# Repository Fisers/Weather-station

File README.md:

# Weather Station
## Included sensors
- Wind Direction (NRG #200P)
- Anenometer (NRG #40)
- Humidity (HIH8131)
- Temperature (HIH8131)
- Atmospheric pressure (BMP280)
## Interface methods
- Ethernet TCP
  - Website interface
  - TCP packets to the server
- Nokia 5110 display
- SD card data logging in CSV format
- ~~USB to UART (For debugging and programming with bootloader)~~ See issues #1
## Power supply
- 100V - 240V AC
- 3.3V DC
## Extras
- Real Time Clock
- Easy calibration using buttons
- Space Invaders minigame
- No easter eggs
## Free PINs for future upgrades
- PB0 (Timer 0) | PA3 (ADC) | PA4 (ADC) | PA5 (ADC) | PA6 (ADC) | PA7 (ADC)
- Motherboard also has free connections to 3.3v and GND aswell as SPI.

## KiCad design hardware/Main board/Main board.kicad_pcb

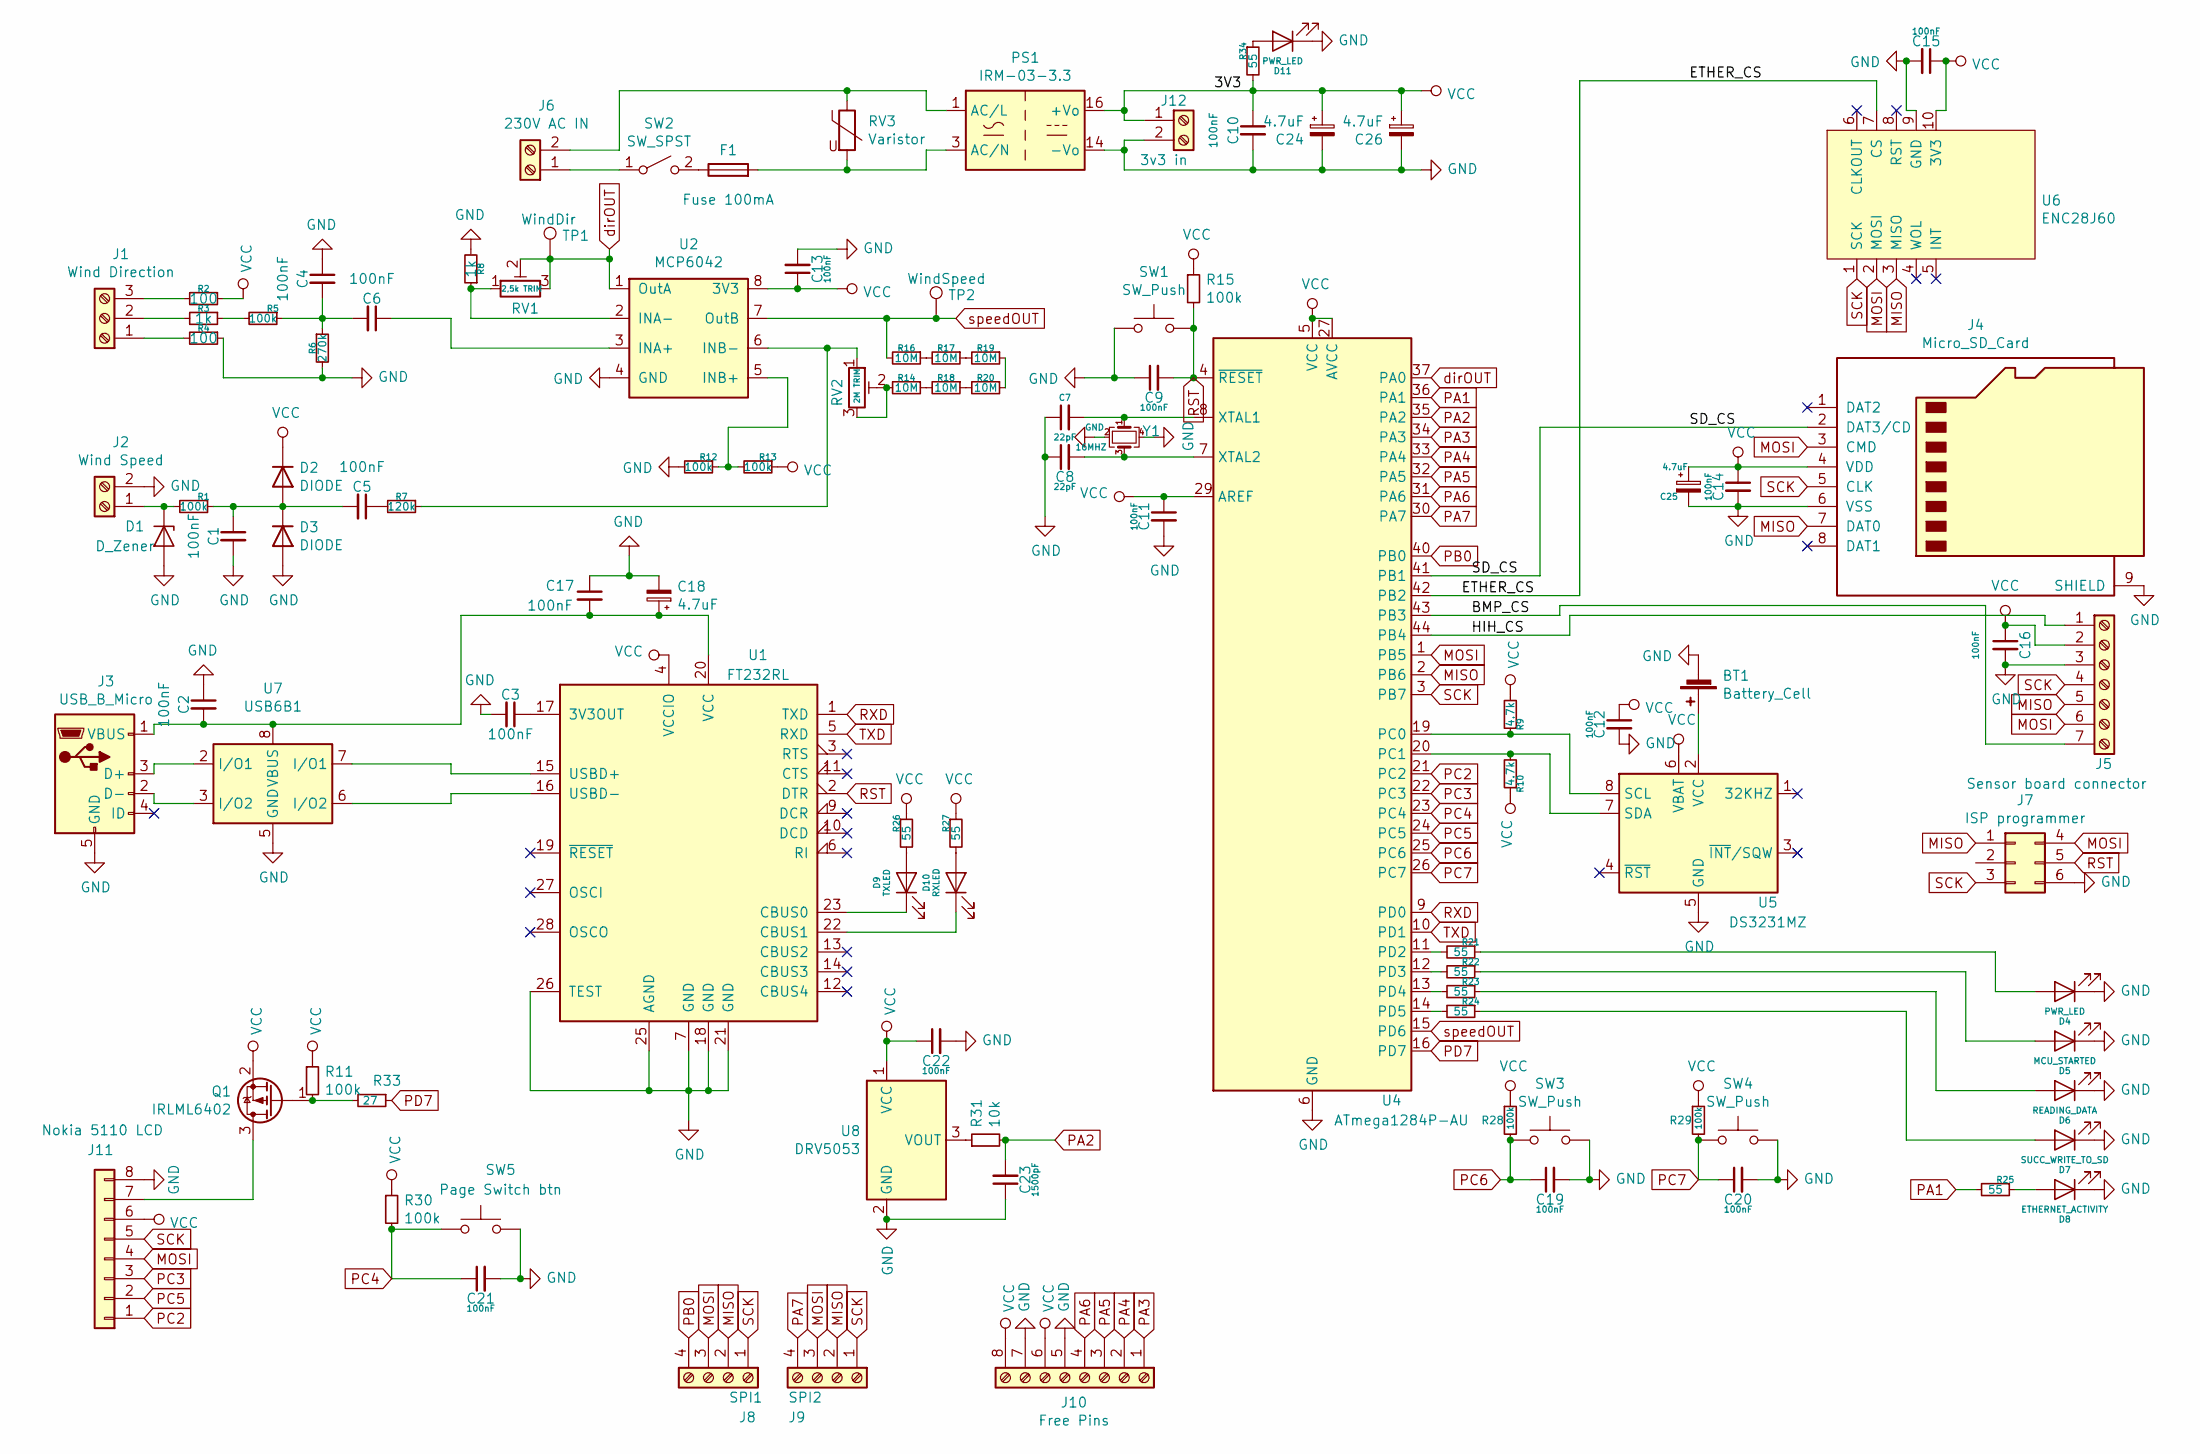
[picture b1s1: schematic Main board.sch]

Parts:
BT1: Battery_Cell; BatteryHolder_Keystone_106_1x20mm
C1, C2, C3, C4, C5, C6, C9, C10, C11, C12, C13, C14, C15, C16, C17, C19, C20, C21, C22: 100nF; C_0805_2012Metric_Pad1.15x1.40mm_HandSolder
C7, C8: 22pF; C_0805_2012Metric_Pad1.15x1.40mm_HandSolder
C18: 4.7uF; CP_Elec_4x5.3
C23: 1500pF; C_0805_2012Metric_Pad1.15x1.40mm_HandSolder
C24, C25, C26: 4.7uF; CP_Elec_4x5.4
D1: D_Zener; D_0805_2012Metric
D2, D3: DIODE; D_0805_2012Metric
D4, D11: PWR_LED; D_0805_2012Metric
D5: MCU_STARTED; D_0805_2012Metric
D6: READING_DATA; D_0805_2012Metric
D7: SUCC_WRITE_TO_SD; D_0805_2012Metric
D8: ETHERNET_ACTIVITY; D_0805_2012Metric
D9: TXLED; D_0805_2012Metric
D10: RXLED; D_0805_2012Metric
F1: Fuse 100mA; Fuseholder_Cylinder-5x20mm_Schurter_0031_8201_Horizontal_Op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
J1: Wind Direction; TerminalBlock_Altech_AK300-4_P5.00mm
J2: Wind Speed; TerminalBlock_Altech_AK300-2_P5.00mm
J3: USB_B_Micro; KYCON_KMMVX-SMT-BS-BTR
J4: Micro_SD_Card; microSD
J5: Sensor board connector; TerminalBlock_Phoenix_MKDS-1,5-8_1x08_P5.00mm_Horizontal
J6: 230V AC IN; TerminalBlock_RND_205-00298_1x02_P10.00mm_Horizontal
J7: ISP programmer; PinHeader_2x03_P2.54mm_Vertical
J8: SPI1; TerminalBlock_Altech_AK300-4_P5.00mm
J9: SPI2; TerminalBlock_Altech_AK300-4_P5.00mm
J10: Free Pins; TerminalBlock_Phoenix_MKDS-1,5-8_1x08_P5.00mm_Horizontal
J11: Nokia 5110 LCD; Nokia_5110_LCD
J12: 3v3 in; TerminalBlock_Altech_AK300-2_P5.00mm
PS1: IRM-03-3.3; Converter_ACDC_MeanWell_IRM-03-xx_THT
Q1: IRLML6402; SOT-23
R1, R5, R11, R12, R13, R15, R28, R29, R30: 100k; R_0805_2012Metric
R2, R4: 100; R_0805_2012Metric
R3, R8: 1k; R_0805_2012Metric
R6: 270k; R_0805_2012Metric
R7: 120k; R_0805_2012Metric
R9, R10: 4.7k; R_0805_2012Metric
R14, R16, R17, R18, R19, R20: 10M; R_0805_2012Metric
R21, R22, R23, R24, R25, R26, R27, R34: 55; R_0805_2012Metric
R31: 10k; R_0805_2012Metric
R33: 27; R_0805_2012Metric
RV1: 2,5k TRIM; Potentiometer_Bourns_3314G_Vertical
RV2: 2M TRIM; Potentiometer_Bourns_3224W_Vertical
RV3: Varistor; Varistor_SMD
SW1, SW3, SW4: SW_Push; SW_Push_1P1T_NO_6x6mm_H9.5mm
SW2: SW_SPST; Switch_NEW
SW5: Page Switch btn; SW_Push_1P1T_NO_6x6mm_H9.5mm
TP1: WindDir; Test_Pad
TP2: WindSpeed; Test_Pad
U1: FT232RL; SSOP-28_5.3x10.2mm_P0.65mm
U2: MCP6042; MCP6042-E&slash_P
U4: ATmega1284P-AU; TQFP-44_10x10mm_P0.8mm
U5: DS3231MZ; SOIC-8_3.9x4.9mm_P1.27mm
U6: ENC28J60
U7: USB6B1; SOIC-8_3.9x4.9mm_P1.27mm
U8: DRV5053; PinSocket_1x03_P2.54mm_Vertical
Y1: 16MHZ; Crystal_SMD

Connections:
/BMP_CS: J5.7, U4.43 (PB3)
/ETHER_CS: U4.42 (PB2), U6.7 (CS)
/HIH_CS: J5.1, U4.44 (PB4)
/SD_CS: J4.2 (DAT3/CD), U4.41 (PB1)
GND: BT1.2 (-), C1.2, C2.1, C3.2, C4.1, C7.1, C8.1, C9.1, C10.2, C11.2, C12.2, C13.2, C14.2, C15.2, C16.2, C17.1, C18.2, C19.2, C20.2, C21.2, C22.2, C23.1, C24.2, C25.2, C26.2, D1.2 (A), D3.1 (A), D4.1 (K), D5.1 (K), D6.1 (K), D7.1 (K), D8.1 (K), D11.1 (K), J2.2, J3.5 (GND), J4.6 (VSS), J4.9 (SHIELD), J5.3, J7.6, J10.5, J10.7, J11.8, J12.2, PS1.14 (-Vo), R4.1, R6.2, R8.2, R12.2, SW1.1, SW3.2, SW4.2, SW5.2, U1.7 (GND), U1.18 (GND), U1.21 (GND), U1.25 (AGND), U1.26 (TEST), U2.4 (GND), U4.6 (GND), U4.18 (GND), U4.28 (GND), U4.39 (GND), U5.5 (GND), U6.9 (GND), U7.4 (GND), U7.5 (GND), U8.2 (GND), Y1.2, Y1.4
MISO: J4.7 (DAT0), J5.5, J7.1, J8.2, J9.2, U4.2 (PB6), U6.3 (MISO)
MOSI: J4.3 (CMD), J5.6, J7.4, J8.3, J9.3, J11.4, U4.1 (PB5), U6.2 (MOSI)
unnamed: BT1.1 (+), U5.2 (VCC)
unnamed: C1.1, C5.2, D2.1 (A), D3.2 (K), R1.1
unnamed: C3.1, U1.17 (3V3OUT)
unnamed: C4.2, C6.2, R5.1, R6.1
unnamed: C5.1, R7.2
unnamed: C6.1, U2.3 (INA+)
unnamed: C7.2, U4.8 (XTAL1), Y1.1
unnamed: C8.2, U4.7 (XTAL2), Y1.3
unnamed: C2.2, C17.2, C18.1, J3.1 (VBUS), U1.20 (VCC), U7.1 (VBUS), U7.8 (VBUS)
unnamed: D1.1 (K), J2.1, R1.2
unnamed: D4.2 (A), R21.1
unnamed: D5.2 (A), R22.1
unnamed: D6.2 (A), R23.1
unnamed: D7.2 (A), R24.1
unnamed: D8.2 (A), R25.1
unnamed: D9.1 (K), U1.23 (CBUS0)
unnamed: D9.2 (A), R26.2
unnamed: D10.1 (K), U1.22 (CBUS1)
unnamed: D10.2 (A), R27.2
unnamed: D11.2 (A), R34.1
unnamed: F1.1, SW2.2 (B)
unnamed: F1.2, PS1.3 (AC/N), RV3.2
unnamed: J1.1, R4.2
unnamed: J1.2, R3.2
unnamed: J1.3, R2.2
unnamed: J3.2 (D-), U7.3 (I/O2)
unnamed: J3.3 (D+), U7.2 (I/O1)
unnamed: J6.1, SW2.1 (A)
unnamed: J6.2, PS1.1 (AC/L), RV3.1
unnamed: J11.7, Q1.3 (D)
unnamed: Q1.1 (G), R11.2, R33.2
unnamed: R3.1, R5.2
unnamed: R7.1, RV2.1, U2.6 (INB-)
unnamed: R8.1, RV1.1, U2.2 (INA-)
unnamed: R9.1, U4.19 (PC0), U5.8 (SCL)
unnamed: R10.2, U4.20 (PC1), U5.7 (SDA)
unnamed: R12.1, R13.2, U2.5 (INB+)
unnamed: R14.1, R18.2
unnamed: R14.2, RV2.2, RV2.3
unnamed: R16.1, R17.2
unnamed: R17.1, R19.2
unnamed: R18.1, R20.2
unnamed: R19.1, R20.1
unnamed: R21.2, U4.11 (PD2)
unnamed: R22.2, U4.12 (PD3)
unnamed: R23.2, U4.13 (PD4)
unnamed: R24.2, U4.14 (PD5)
unnamed: R31.1, U8.3 (VOUT)
unnamed: U1.15 (USBD+), U7.7 (I/O1)
unnamed: U1.16 (USBD-), U7.6 (I/O2)
PA1: R25.2, U4.36 (PA1)
PA2: C23.2, R31.2, U4.35 (PA2)
PA3: J10.1, U4.34 (PA3)
PA4: J10.2, U4.33 (PA4)
PA5: J10.3, U4.32 (PA5)
PA6: J10.4, U4.31 (PA6)
PA7: J9.4, U4.30 (PA7)
PB0: J8.4, U4.40 (PB0)
PC2: J11.1, U4.21 (PC2)
PC3: J11.3, U4.22 (PC3)
PC4: C21.1, R30.2, SW5.1, U4.23 (PC4)
PC5: J11.2, U4.24 (PC5)
PC6: C19.1, R28.2, SW3.1, U4.25 (PC6)
PC7: C20.1, R29.2, SW4.1, U4.26 (PC7)
PD7: R33.1, U4.16 (PD7)
RST: C9.2, J7.5, R15.2, SW1.2, U1.2 (DTR), U4.4 (~RESET)
RXD: U1.1 (TXD), U4.9 (PD0)
SCK: J4.5 (CLK), J5.4, J7.3, J8.1, J9.1, J11.5, U4.3 (PB7), U6.1 (SCK)
TXD: U1.5 (RXD), U4.10 (PD1)
VCC: C10.1, C11.1, C12.1, C13.1, C14.1, C15.1, C16.1, C22.1, C24.1, C25.1, C26.1, D2.2 (K), J4.4 (VDD), J5.2, J10.6, J10.8, J11.6, J12.1, PS1.16 (+Vo), Q1.2 (S), R2.1, R9.2, R10.1, R11.1, R13.1, R15.1, R26.1, R27.1, R28.1, R29.1, R30.1, R34.2, U1.4 (VCCIO), U2.8 (3V3), U4.5 (VCC), U4.17 (VCC), U4.27 (AVCC), U4.29 (AREF), U4.38 (VCC), U5.6 (VBAT), U6.10 (3V3), U8.1 (VCC)
dirOUT: RV1.2, RV1.3, TP1.1, U2.1 (OutA), U4.37 (PA0)
speedOUT: R16.2, TP2.1, U2.7 (OutB), U4.15 (PD6)

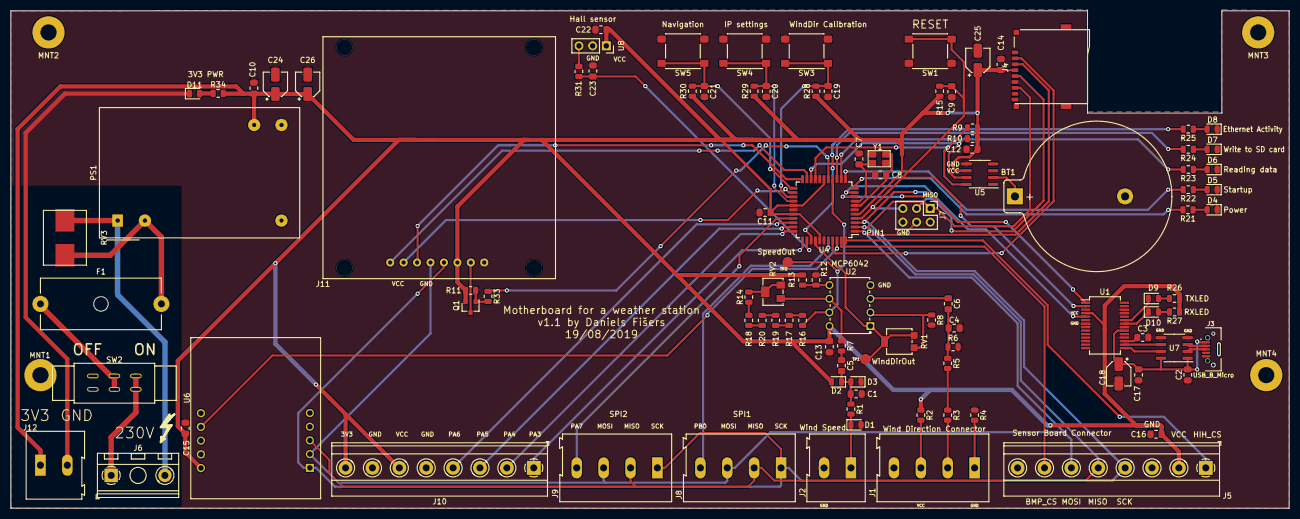
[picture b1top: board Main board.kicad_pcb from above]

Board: 2 copper layers, 237.8 x 92.5 mm, 108 parts (0 on the bottom side), 79 nets.

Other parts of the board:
MNT1, MNT2, MNT3, MNT4: MountingHole_3mm_Pad

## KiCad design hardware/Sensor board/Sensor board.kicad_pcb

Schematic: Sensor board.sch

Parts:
C1, C2: C_Small; C_0805_2012Metric_Pad1.15x1.40mm_HandSolder
J1: Conn_01x07_Female; PinSocket_1x07_P2.54mm_Vertical
J2: bmp280; PinSocket_1x07_P2.54mm_Vertical
R1: R_Small; R_0805_2012Metric_Pad1.15x1.40mm_HandSolder
U1: HIH8130; SOIC-8_3.9x4.9mm_P1.27mm

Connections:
/BMP280_CS: J1.7, J2.7
/CLK: J1.4, J2.4, U1.4
/MISO: J1.5, J2.5, U1.5
/MOSI: J1.6, J2.6
GND: C1.1, C2.1, J1.3, J2.3, U1.2
unnamed: C2.2, U1.1
unnamed: J1.1, R1.2, U1.3
VCC: C1.2, J1.2, J2.2, R1.1, U1.8

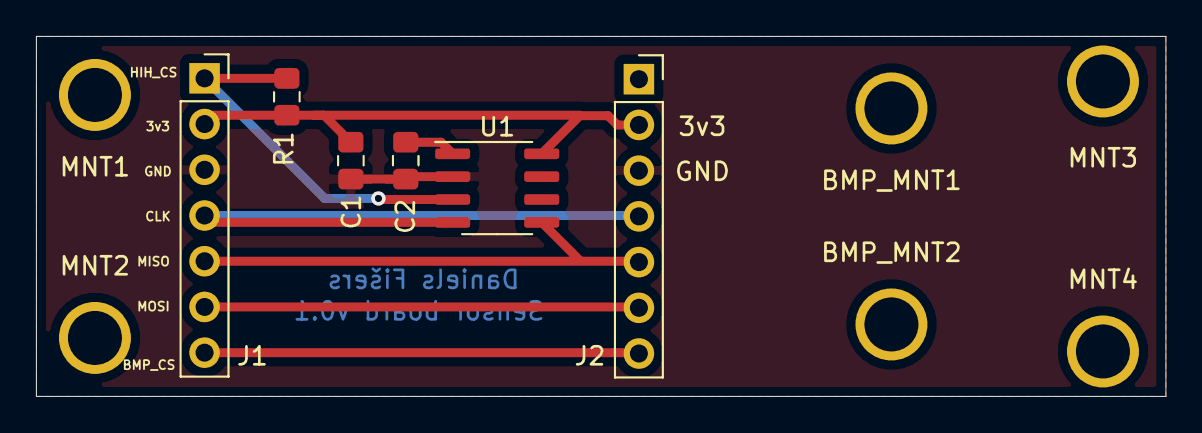
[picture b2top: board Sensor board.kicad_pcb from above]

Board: 2 copper layers, 62.8 x 20.0 mm, 12 parts (0 on the bottom side), 8 nets.

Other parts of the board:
BMP_MNT1, BMP_MNT2: MountingHole_3mm_Pad
MNT1, MNT2, MNT3, MNT4: MountingHole_3mm_Pad

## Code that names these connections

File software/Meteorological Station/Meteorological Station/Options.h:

/*
 * Options.h
 *
 * Created: 11/07/2019 10:34:09
 *  Author: daniels
 */ 


#ifndef OPTIONS_H_
#define OPTIONS_H_

#include "includes/RTC/rtc.h"

#define F_CPU 16000000UL // Defining the CPU Frequency for Delay Calculation in delay.h
#define BAUD 9600
#define PORT_CS PORTB
#define BMP_CS PINB3
#define ETHER_CS PINB2
#define SD_CS PINB1
#define HIH_CS PINB4

#define PORT_LCD PORTC
#define PORT_SPI PORTB
#define DDR_SPI DDRB
#define DDR_LCD DDRC

/*
 * LCD's pins
 */
#define LCD_SCE PC5
#define LCD_RST PC2
#define LCD_DC PC3
#define LCD_DIN PB5
#define LCD_CLK PB7

extern unsigned int magnetVal;
extern unsigned int halleff;
extern unsigned int timeout; // in seconds
extern rtc_t rtc;

extern uint8_t myip[4];
extern char serverip[16];
extern uint8_t gwip[4];


extern char humidChar[10],tempChar[10],pressChar[16],anglChar[10],speedChar[10];

void stringToIntArray(uint8_t * array, char * string, uint8_t * eepromAddr);



#endif /* OPTIONS_H_ */

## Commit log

2019-06-28 Add wind
2019-06-28 Convert SIP-4 to 2.54mm for use in breadboard
2019-06-28 Arduino code for measuring wind speed and direction
2019-07-05 AVR version for wind direction and atmospheric pressure
2019-07-16 Meteorological Station for AVR with TCP and SD card data logging
2019-07-17 Sensor board for HIH8131 and BMP280 for use in a radiation shield.
2019-07-19 Added main board.
2019-07-19 Added a main board schematic
2019-07-22 Updated the board with nokia 5110 display.
2019-07-23 Finished the schematic for the main board
2019-07-23 Updated main board
2019-07-24 Finished the board design
2019-07-25 Added 0 new easter eggs
2019-07-26 Improved the design of the PCB
2019-07-26 Updated the main board to v0.5
2019-07-26 Main board update
2019-07-26 Minor update to the main board
2019-07-26 Added button labels
2019-07-29 Added protection for power input
2019-07-29 Updated the power supply input
2019-07-29 Changed varistor footprint
2019-07-30 Updated the footprint to fit radiation shield
2019-07-31 Changed a few pins
2019-07-31 Slight improvements to the board
2019-07-31 Slight adjustments
2019-08-14 Fixed multiple things
2019-08-19 Fixed multiple issues
2019-08-20 Close to a finished product
2019-08-27 Added new 3D models
2019-08-27 Motherboard version v1.1
2019-08-29 Code for the weather station v1.1 released
2019-08-29 Added an manual on how to operate the weather station

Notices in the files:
parts and their libraries:
Copyright 2016 Accelerated Designs. All rights reserved.
